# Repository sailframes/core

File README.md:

# SailFrames

Open-source sailboat racing data logger and analytics platform.

[sailframes.com](https://sailframes.com) | [github.com/sailframes](https://github.com/sailframes) | Apache 2.0 License

## What is SailFrames?

SailFrames is a self-contained, waterproof data acquisition device for competitive sailboat racing. It captures high-precision GPS tracks, wind speed and direction, boat motion (heel/pitch/heading), barometric pressure, and cockpit video — all synchronized with GPS timestamps. Data syncs to AWS after each session for web-based race analysis and replay.

## Repository Structure

```
sailframes/core/
├── edge-s/            # Raspberry Pi edge device
│   ├── services/      # Sensor acquisition (GPS, IMU, wind, pressure, camera)
│   ├── scripts/       # Install, start, stop, Wi-Fi mode
│   ├── config/        # Device configuration
│   └── tests/         # Sensor connectivity tests
├── edge-e/            # ESP32 edge device
│   ├── hardware/      # KiCad PCB designs
│   └── firmware/      # ESP32 Arduino firmware
├── web/               # Dashboard web application
│   ├── api/           # Backend API
│   └── frontend/      # React frontend
├── lambda/            # AWS Lambda functions
├── processing/        # Post-race data processing
├── infrastructure/    # AWS CDK/Terraform
├── scripts/           # Utility scripts
├── services/          # Systemd service definitions
├── config/            # Shared configuration
└── tests/             # Integration tests
```

## Hardware

| Component | Part | Interface |
|-----------|------|-----------|
| Compute | Raspberry Pi 5 | — |
| GPS | u-blox ZED-F9P | USB |
| Wind | Calypso Ultrasonic Mini | BLE 5.1 |
| IMU | BNO085 (GY-BNO08X) | I2C @ 0x4A |
| Pressure | DPS310 | I2C @ 0x77 |
| Camera | Pi Camera 3 Wide | CSI |
| Display | 1602 LCD + PCF8574T | I2C @ 0x27 |
| Enclosure | IP67 sealed | Gore-Tex vent |

## Quick Start (Edge Device)

```bash
# Clone the repo
git clone https://github.com/sailframes/core.git
cd core

# Run the installer on Raspberry Pi
sudo bash edge-s/scripts/install.sh

# Test all sensors
python3 edge-s/tests/test_gps.py
python3 edge-s/tests/test_imu.py
python3 edge-s/tests/test_pressure.py
python3 edge-s/tests/test_wind.py
python3 edge-s/tests/test_camera.py

# Start all services
sudo bash edge-s/scripts/start.sh

# Check status
sudo systemctl status sailframes-*
```

## Data Format

All sensor data is timestamped with GPS time (UTC):

```
/mnt/sailframes-data/
├── 2026-03-15/
│   ├── gps/
│   │   └── track_20260315_140000.csv
│   ├── imu/
│   │   └── imu_20260315_140000.csv
│   ├── pressure/
│   │   └── pressure_20260315_140000.csv
│   ├── wind/
│   │   └── wind_20260315_140000.csv
│   └── video/
│       └── cockpit_20260315_140000.mp4
```

## Fleet

- 6 devices deployed
- Sonar 23 and J/80 class boats
- Boston Harbor, Massachusetts

## License

Apache 2.0

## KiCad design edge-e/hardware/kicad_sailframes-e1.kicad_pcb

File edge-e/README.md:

# SailFrames Edge-E

ESP32-based edge device for sailboat racing data acquisition.

Part of [sailframes/core](https://github.com/sailframes/core). See [edge-s](../edge-s) for Raspberry Pi-based device.

## Variants

- **E1** - First generation ESP32 device (current)

## Hardware (E1)

| Component | Part | Interface |
|-----------|------|-----------|
| MCU | ESP32 | — |
| GPS | u-blox | UART |
| IMU | ICM-20948 or BNO085 | I2C |
| Storage | MicroSD | SPI |

## Directory Structure

```
edge-e/
├── hardware/          # KiCad PCB designs
│   ├── *.kicad_sch    # Schematic
│   ├── *.kicad_pcb    # PCB layout
│   └── *.kicad_pro    # Project file
└── firmware/          # ESP32/Arduino firmware
    └── sailframes_e1/ # E1 device firmware
```

## KiCad

Open the project in KiCad 8+:

```bash
cd edge-e/hardware
kicad kicad_sailframes-e1.kicad_pro
```

## Firmware

Build and flash using Arduino IDE or PlatformIO:

```bash
cd edge-e/firmware/sailframes_e1
# Open in Arduino IDE or use PlatformIO
```

## Edge-S vs Edge-E

| Feature | Edge-S (Pi) | Edge-E (ESP32) |
|---------|-------------|----------------|
| Camera | Yes (Pi Camera 3) | No |
| Video recording | Yes | No |
| Dashboard | Yes (web server) | No |
| Power consumption | ~5-7W | <1W |
| Cost | Higher | Lower |
| Use case | Full data + video | Lightweight logging |

## License

Apache 2.0

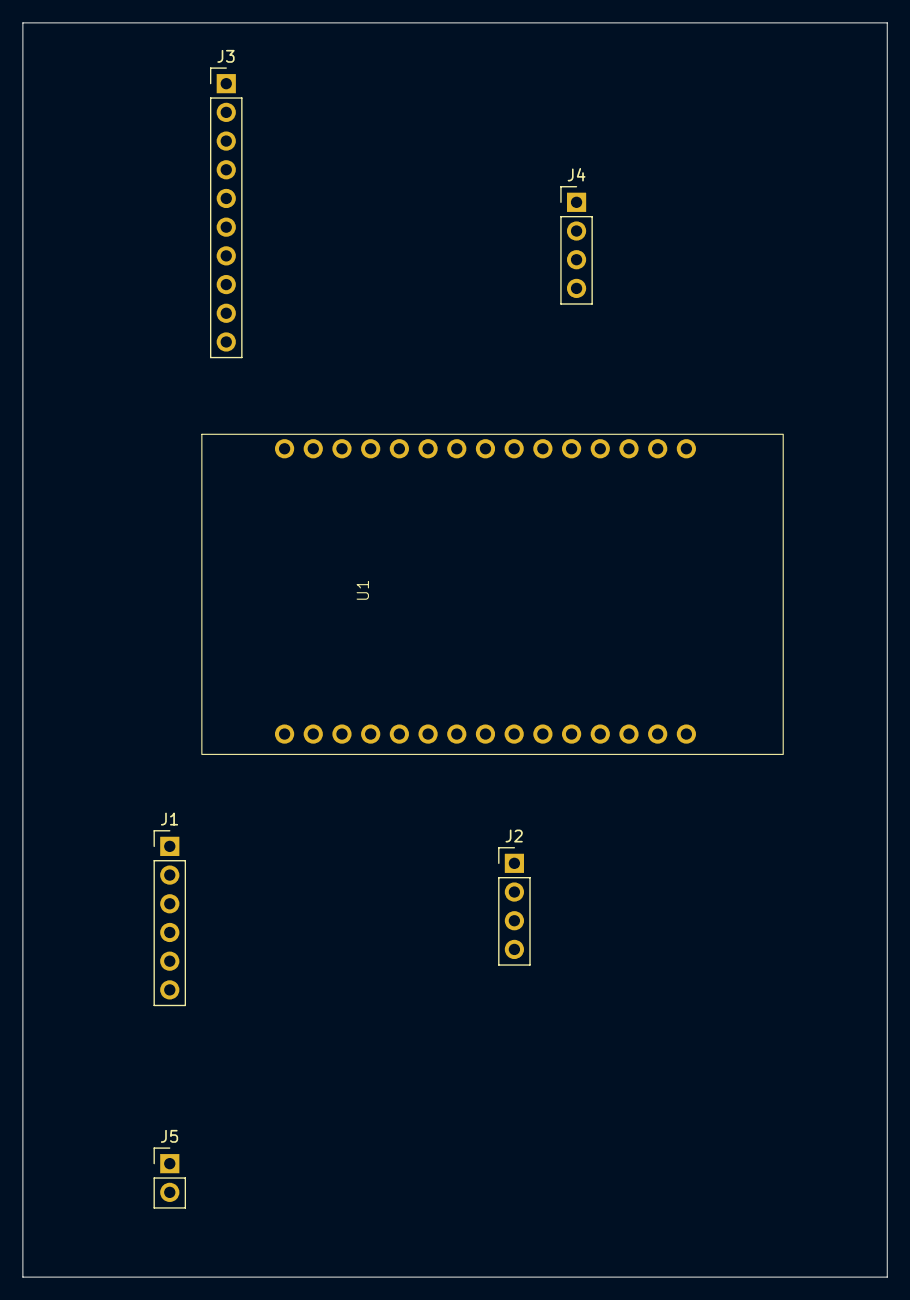
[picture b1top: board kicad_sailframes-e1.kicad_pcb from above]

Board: 2 copper layers, 76.5 x 111.0 mm, 6 parts (0 on the bottom side), 11 nets, no tracks yet.

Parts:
J1: Conn_01x06; SD_CARD
J2, J4: Conn_01x04; PinHeader_1x04_P2.54mm_Vertical
J3: Conn_01x10; PinHeader_1x10_P2.54mm_Vertical
J5: Conn_01x02; PinHeader_1x02_P2.54mm_Vertical
U1: ESP32DEVIKITV1

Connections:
/3V3: J1.1, J3.1, J4.2, U1.16 (3V3)
/5V_IN: J2.3, J5.1, U1.15 (VIN)
/GND: J1.6, J2.4, J3.2, J4.1, J5.2, U1.14 (GND), U1.17 (GND)
/GPS_RX: J2.2, U1.22 (TX2)
/GPS_TX: J2.1, U1.21 (RX2)
/MISO: J1.5, U1.25 (D19)
/MOSI: J1.3, U1.30 (D23)
/SCK: J1.4, U1.24 (D18)
/SCL: J3.3, J4.3, U1.29 (D22)
/SDA: J3.4, J4.4, U1.26 (D21)
/SD_CS: J1.2, U1.23 (D5)

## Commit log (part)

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2026-03-23 Add analysis web dashboard with processing engine, React frontend, and export tools
    - processing/: Offline analysis engine with tack/gybe detection, straight-line
    leg segmentation, true wind calculation, polar diagram generation, VMG
    computation, violin plot statistics, and correlation analysis
    - web/api/: FastAPI backend serving analysis results, sessions, boats,
    leaderboard, and video endpoints (supports S3 and local data)
    - web/frontend/: React + Vite dashboard with Plotly charts including
2026-03-30 Fix GPS config script error handling
2026-04-01 Move CPU temp section higher to avoid SAT overlap
2026-04-02 D2: show fix type instead of SAT label
2026-04-02 D2: larger fonts for wind/nav rows, pitch in status line
2026-04-02 Fix E1 upload URL: add /prod stage path
2026-04-03 Add video controls to dashboard
2026-04-03 Fix video sync with unified timeline
2026-04-03 Fix battery monitoring GPIO35 pullup and false critical detection
2026-04-03 Fix video sync: handle timeline before/after video range
2026-04-07 Fix TWS/TWA formulas: wrong signs caused incorrect wind calculations
    TWS formula had + instead of - (2·AWS·SOG·cos(AWA) term).
    TWA formula had + SOG instead of - SOG, producing ~329° instead
    of the correct angle. Comments showed the right formulas but
    code implemented them with inverted signs.
    Also added wind_offset config parameter (degrees) for sensor
    mounting calibration — set in config.txt if Calypso bow mark
2026-04-09 Fix E1 crash: remove duplicate WiFi upload path racing with Core 0 task
    checkWiFiUpload() on the main loop and uploadTaskFunc() on Core 0 could
    both trigger uploads simultaneously. checkWiFiUpload() accessed SD without
    sdMutex, and uploadTaskFunc() never deinited BLE before WiFi — both caused
    crashes.
    Fix: remove checkWiFiUpload() entirely, make uploadTaskFunc() the single
    owner of all upload operations with BLE deinit/reinit, stationary check,
2026-04-09 E1: keep IMU/pressure sensors running during WiFi upload
    Upload now runs entirely on Core 0, sensor reads are I2C on Core 1 — no
    conflict. SD logging is already guarded by the `logging` flag which is
    always false during upload. No reason to blank out heel/pitch/pressure
    on the display while uploading.
    https://claude.ai/code/session_019i1uJZTk7fZJ9ZwSkWvr92
2026-04-09 E1: stop deiniting BLE during WiFi upload — no longer needed
    BLE deinit was required when uploads used TLS (mbedTLS needed ~50KB heap,
    BLE competed for memory). Uploads now use plain HTTP to S3 — no TLS memory
    pressure. ESP32 can time-slice WiFi and BLE on the shared radio for basic
    HTTP PUTs. Wind sensor stays connected during uploads.
    https://claude.ai/code/session_019i1uJZTk7fZJ9ZwSkWvr92
2026-04-09 E1: replace fullscreen UPLOADING display with small status line indicator
    Upload runs on Core 0 and no longer interrupts sensors, so the display
    should keep showing live sensor data. Upload progress now shows as
    "UP3/10" in the bottom status line alongside other indicators (rec state,
    WiFi, wind). Removed the large UPLOADING overlay with progress bar.
    https://claude.ai/code/session_019i1uJZTk7fZJ9ZwSkWvr92
